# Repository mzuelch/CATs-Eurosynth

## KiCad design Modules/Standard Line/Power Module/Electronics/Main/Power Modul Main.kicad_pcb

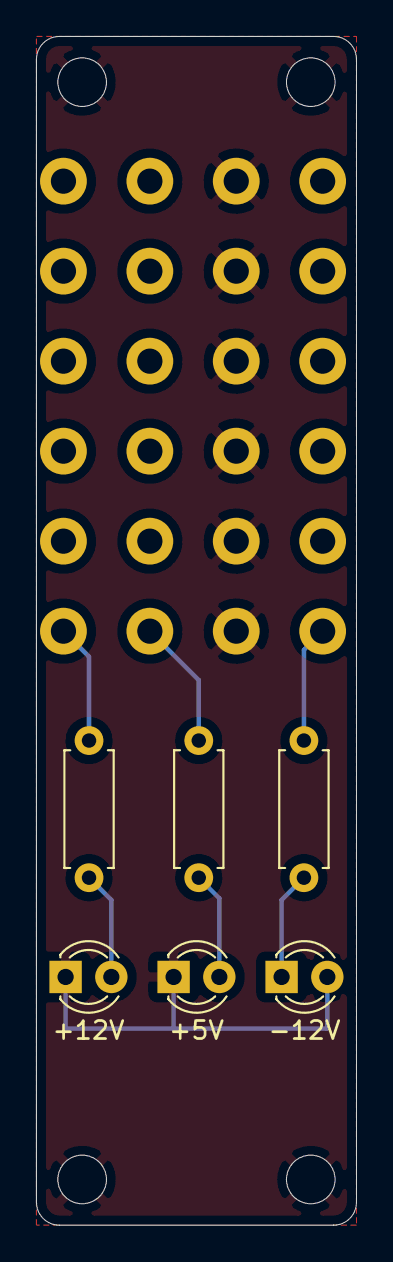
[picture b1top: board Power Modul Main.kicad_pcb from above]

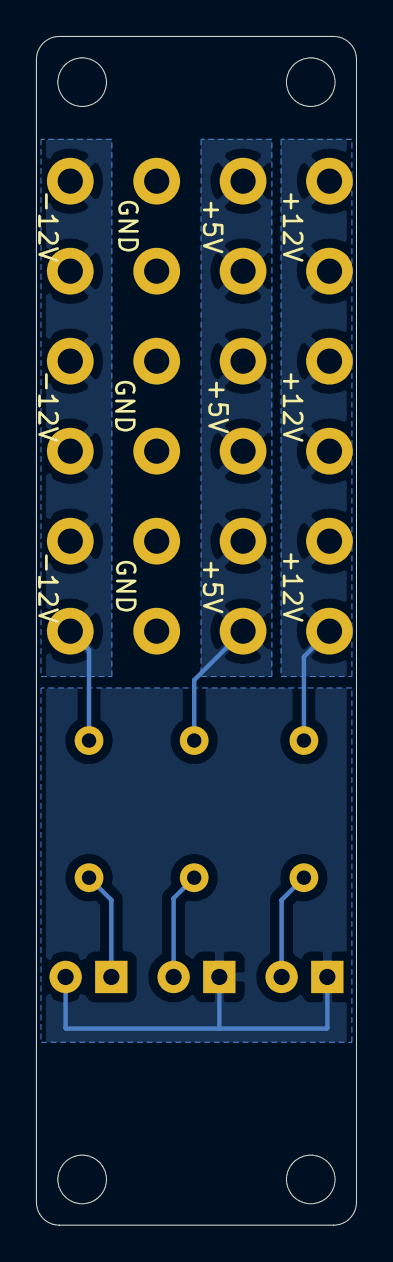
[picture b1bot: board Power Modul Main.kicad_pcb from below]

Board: 2 copper layers, 17.8 x 66.0 mm, 22 parts (4 on the bottom side), 7 nets.

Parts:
D1: +12V; LED_D3.0mm
D2: +5V; LED_D3.0mm
D3: -12V; LED_D3.0mm
H1, H2, H3, H4: MountingHole_Pad; MountingHole_2.7mm
J1, J5, J9: +12V; 03866b.68_6.3mm_FASTON
J2, J6, J10: +5V; 03866b.68_6.3mm_FASTON
J3, J7, J11: GND; 03866b.68_6.3mm_FASTON
J4, J8, J12: -12V; 03866b.68_6.3mm_FASTON
R1, R3: 1k; R_Axial_DIN0207_L6.3mm_D2.5mm_P7.62mm_Horizontal
R2: 200R; R_Axial_DIN0207_L6.3mm_D2.5mm_P7.62mm_Horizontal

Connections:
+5V: J2.1, J6.1, J10.1, R2.1
+12V: J1.1, J5.1, J9.1, R1.1
-12V: J4.1, J8.1, J12.1, R3.2
GND: D1.1, D2.1, D3.2, H1.1, H2.1, H3.1, H4.1, J3.1, J7.1, J11.1
unnamed: D1.2, R1.2
unnamed: D2.2, R2.2
unnamed: D3.1, R3.1

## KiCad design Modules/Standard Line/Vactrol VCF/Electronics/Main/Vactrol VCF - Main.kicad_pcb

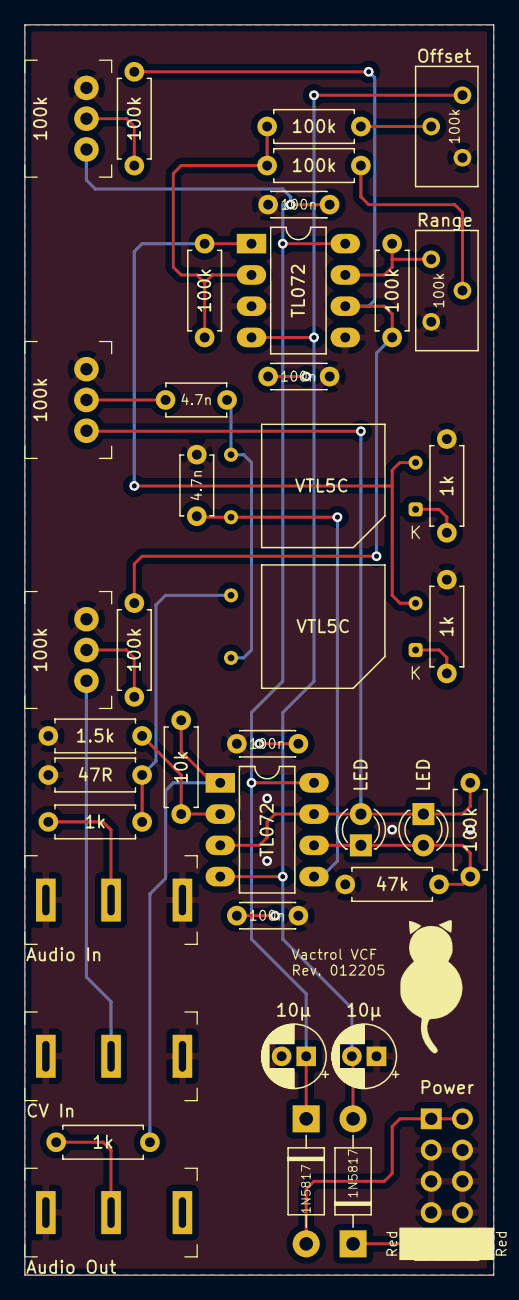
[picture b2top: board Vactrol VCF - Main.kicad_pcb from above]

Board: 2 copper layers, 38.1 x 101.6 mm, 40 parts (0 on the bottom side), 26 nets.

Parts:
C1, C2: 4.7n; C_Disc_D4.7mm_W2.5mm_P5.00mm
C3, C4: 10µ; CP_Radial_D5.0mm_P2.00mm
C5, C6, C7, C8: 100n; C_Disc_D4.3mm_W1.9mm_P5.00mm
D1, D2: LED; LED_D3.0mm
D3, D4: 1N5817; D_DO-41_SOD81_P10.16mm_Horizontal
J1: Audio In; Jack_3.5mm_QingPu_WQP-PJ323M
J2: Audio Out; Jack_3.5mm_QingPu_WQP-PJ323M
J3: Power; Power_2x5_Vertical
J4: CV In; Jack_3.5mm_QingPu_WQP-PJ323M
P1, P2, P3: 100k; Potentiometer_AlpsAlpine_RK0971110
R1, R3, R4, R12: 1k; R_Axial_DIN0207_L6.3mm_D2.5mm_P7.62mm_Horizontal
R2: 47R; R_Axial_DIN0207_L6.3mm_D2.5mm_P7.62mm_Horizontal
R5: 47k; R_Axial_DIN0207_L6.3mm_D2.5mm_P7.62mm_Horizontal
R6, R7, R8, R9, R13, R14, R15: 100k; R_Axial_DIN0207_L6.3mm_D2.5mm_P7.62mm_Horizontal
R10: 1.5k; R_Axial_DIN0207_L6.3mm_D2.5mm_P7.62mm_Horizontal
R11: 10k; R_Axial_DIN0207_L6.3mm_D2.5mm_P7.62mm_Horizontal
RV1, RV2: 100k; Potentiometer_Bourns_3296Y_Vertical
U1, U2: VTL5C; PerkinElmer_VTL5C
U3, U4: TL072; DIP-8_W7.62mm_LongPads

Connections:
+12V: C3.1, C5.1, C7.1, D3.1, P2.CW, U3.8, U4.8
-12V: C4.2, C6.2, C8.2, D4.2, RV1.3, U3.4, U4.4
GND: C2.1, C3.2, C4.1, C5.2, C6.1, C7.2, C8.1, J1.S, J1.TN, J2.S, J3.GND, J4.S, J4.TN, P1.CCW, P2.CCW, P3.CCW, R2.2, R3.1, R4.1, R5.1, R10.1, RV1.1, RV2.3, U3.3, U3.5
unnamed: C1.1, P1.W
unnamed: C1.2, U1.3, U2.4
unnamed: C2.2, U2.3, U4.5
unnamed: D1.1, D2.2, R5.2, R7.2, U4.6
unnamed: D1.2, D2.1, P1.CW, R7.1, U4.3, U4.7
unnamed: D3.2, J3.+12V
unnamed: D4.1, J3.-12V
unnamed: J1.T, R1.2
unnamed: J2.T, R12.1
unnamed: J4.T, P3.CW
unnamed: P2.W, R14.1
unnamed: P3.W, R15.1
unnamed: R1.1, R2.1, U1.4
unnamed: R3.2, U1.1
unnamed: R4.2, U2.1
unnamed: R6.1, R8.2, R9.2, U3.2
unnamed: R6.2, U1.2, U2.2, U3.1
unnamed: R8.1, RV1.2
unnamed: R9.1, RV2.2
unnamed: R10.2, R11.2, U4.2
unnamed: R11.1, R12.2, U4.1
unnamed: R13.1, R14.2, R15.2, U3.6
unnamed: R13.2, RV2.1, U3.7

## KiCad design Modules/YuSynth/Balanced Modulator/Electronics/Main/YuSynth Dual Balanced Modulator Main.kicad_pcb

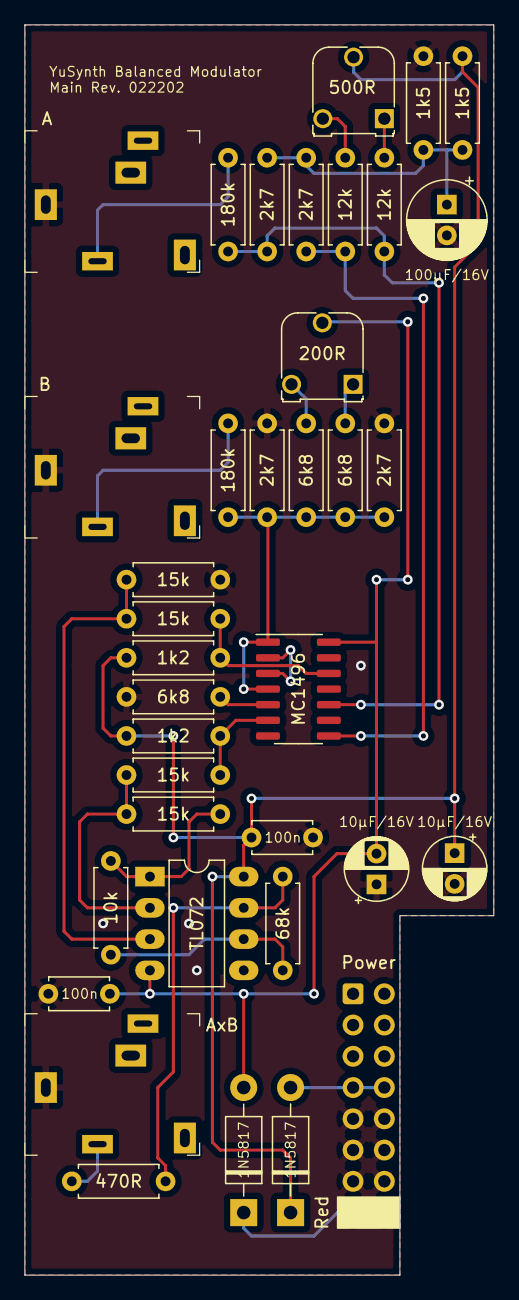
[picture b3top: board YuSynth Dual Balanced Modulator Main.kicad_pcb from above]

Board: 2 copper layers, 38.1 x 101.6 mm, 37 parts (0 on the bottom side), 25 nets.

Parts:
C1: 100µF/16V; CP_Radial_D6.3mm_P2.50mm
C2, C3: 10µF/16V; CP_Radial_D5.0mm_P2.50mm
C4, C5: 100n; C_Disc_D4.7mm_W2.5mm_P5.00mm
D1, D2: 1N5817; D_DO-41_SOD81_P10.16mm_Horizontal
J1: Power; Power_2x8_Horizontal
J2: A; Jack_3.5mm_QingPu_WQP-PJ324M
J3: B; Jack_3.5mm_QingPu_WQP-PJ324M
J4: AxB; Jack_3.5mm_QingPu_WQP-PJ324M
R1, R2: 1k5; R_Axial_DIN0207_L6.3mm_D2.5mm_P7.62mm_Horizontal
R3, R4: 180k; R_Axial_DIN0207_L6.3mm_D2.5mm_P7.62mm_Horizontal
R5, R7, R8, R12: 2k7; R_Axial_DIN0207_L6.3mm_D2.5mm_P7.62mm_Horizontal
R6, R10, R14: 6k8; R_Axial_DIN0207_L6.3mm_D2.5mm_P7.62mm_Horizontal
R9, R11: 12k; R_Axial_DIN0207_L6.3mm_D2.5mm_P7.62mm_Horizontal
R13, R15: 1k2; R_Axial_DIN0207_L6.3mm_D2.5mm_P7.62mm_Horizontal
R16, R17, R18, R19: 15k; R_Axial_DIN0207_L6.3mm_D2.5mm_P7.62mm_Horizontal
R20: 10k; R_Axial_DIN0207_L6.3mm_D2.5mm_P7.62mm_Horizontal
R21: 68k; R_Axial_DIN0207_L6.3mm_D2.5mm_P7.62mm_Horizontal
R22: 470R; R_Axial_DIN0207_L6.3mm_D2.5mm_P7.62mm_Horizontal
RV1: 200R; Potentiometer_Runtron_RM-065_Vertical
RV2: 500R; Potentiometer_Runtron_RM-065_Vertical
U1: MC1496; SOIC-14_3.9x8.7mm_P1.27mm
U2: TL072; DIP-8_W7.62mm_LongPads

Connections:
+6V: C1.1, R1.1, R2.2, R7.2, R8.2
+12V: C2.1, C4.1, D1.1, R1.2, R13.1, R15.1, RV2.2, U2.8
+12VA: D1.2, J1.+12V
-12V: C3.2, C5.2, D2.2, RV1.2, U1.14, U2.4
-12VA: D2.1, J1.-12V
GND: C1.2, C2.2, C3.1, C4.2, C5.1, J1.GND, J2.S, J3.S, J4.S, R2.1, R5.2, R12.1, R14.2, R18.1, U2.5
In_A: J2.T, R3.2
In_B: J3.T, R4.1
unnamed: R3.1, R8.1, R9.2, U1.10
unnamed: R6.2, RV1.3
unnamed: R9.1, RV2.1
unnamed: R4.2, R5.1, R6.1, R10.1, R12.2, U1.1, U1.4
unnamed: R10.2, RV1.1
unnamed: R11.1, RV2.3
unnamed: R7.1, R11.2, U1.8
unnamed: R13.2, R16.1, U1.6
unnamed: R14.1, U1.5
unnamed: R15.2, R17.2, U1.12
unnamed: R16.2, R19.2, U2.2
unnamed: R17.1, R18.2, U2.3
unnamed: R19.1, R20.2, U2.1
unnamed: R20.1, R21.2, U2.6
unnamed: R21.1, R22.2, U2.7
unnamed: U1.2, U1.3
Out: J4.T, R22.1

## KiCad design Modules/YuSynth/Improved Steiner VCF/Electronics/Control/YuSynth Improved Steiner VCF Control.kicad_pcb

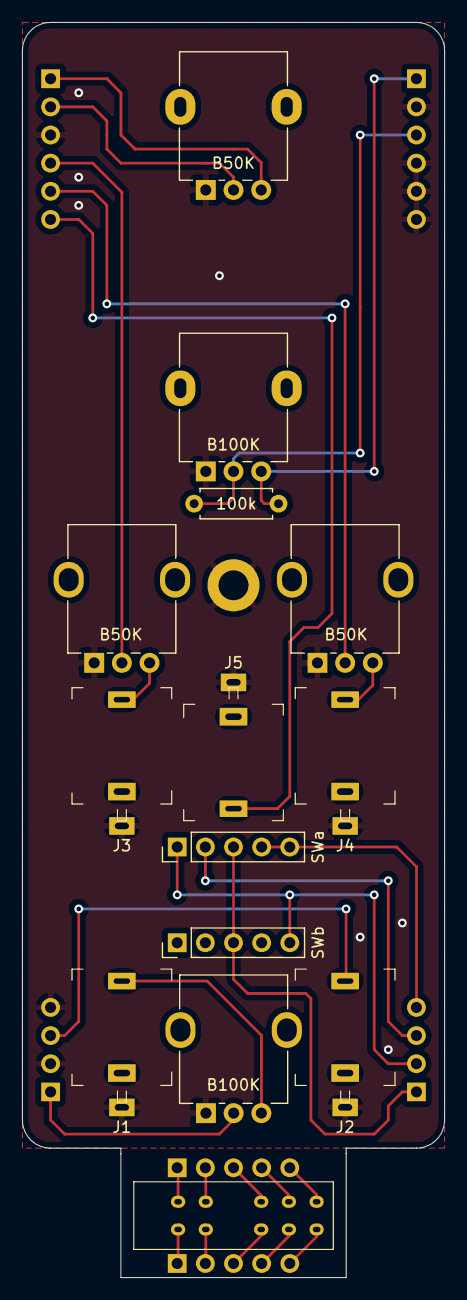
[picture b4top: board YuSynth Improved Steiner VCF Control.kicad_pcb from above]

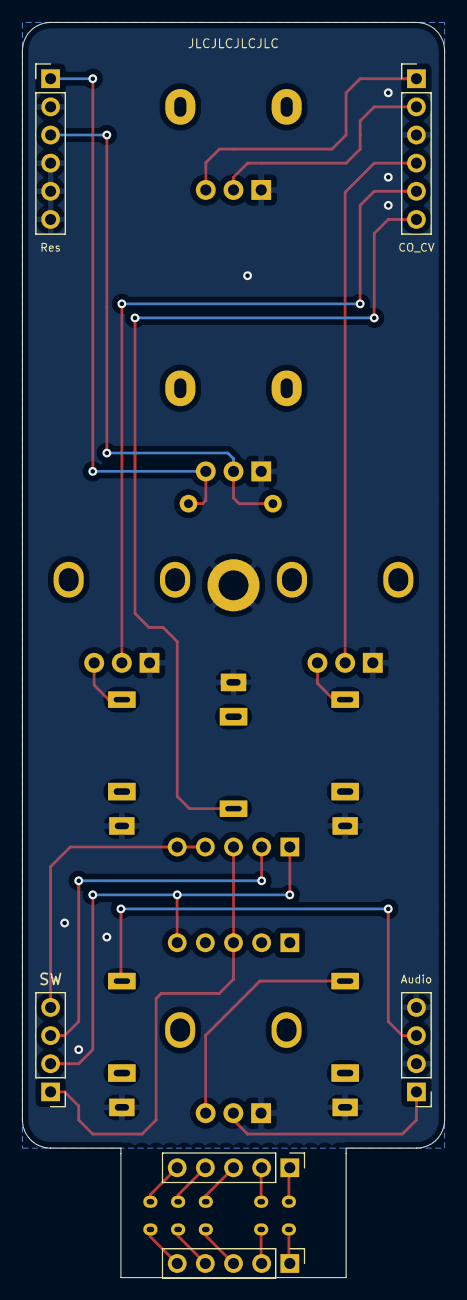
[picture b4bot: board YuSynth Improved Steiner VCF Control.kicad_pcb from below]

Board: 2 copper layers, 38.1 x 113.3 mm, 21 parts (6 on the bottom side), 22 nets.

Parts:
H1: MountingHole_Pad; MountingHole_2.7mm_M2.5_DIN965_Pad
J1: Audio In; Jack_3.5mm_QingPu_WQP-PJ301M-12
J2: Audio Out; Jack_3.5mm_QingPu_WQP-PJ301M-12
J3: CV#1; Jack_3.5mm_QingPu_WQP-PJ301M-12
J4: CV#2; Jack_3.5mm_QingPu_WQP-PJ301M-12
J5: V/Oct; Jack_3.5mm_QingPu_WQP-PJ301M-12
J6, J12: SWb; PinHeader_1x05_P2.54mm_Vertical
J7, J13: SWa; PinHeader_1x05_P2.54mm_Vertical
J8: Audio; PinHeader_1x04_P2.54mm_Vertical
J9: SW; PinHeader_1x04_P2.54mm_Vertical
J10: CO_CV; PinHeader_1x06_P2.54mm_Vertical
J11: Res; PinHeader_1x06_P2.54mm_Vertical
R1: 100k; R_Axial_DIN0207_L6.3mm_D2.5mm_P7.62mm_Horizontal
RV1, RV5: B100K; Potentiometer_Alpha_RD901F-40-00D_Single_Vertical
RV2, RV3, RV4: B50K; Potentiometer_Alpha_RD901F-40-00D_Single_Vertical
SW1: Mode; SS24E01-G5

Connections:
AudioOut: J2.T, J8.3
GND: H1.1, J1.S, J2.S, J3.S, J4.S, J5.S, J8.2, J8.4, J10.3, J11.2, J11.4, J11.5, J11.6, RV1.1, RV2.1, RV3.1, RV4.1, RV5.1
unnamed: J1.T, RV1.3
unnamed: J3.T, RV3.3
unnamed: J4.T, RV2.3
unnamed: J12.1, SW1.1
unnamed: J12.2, SW1.2
unnamed: J12.3, SW1.3
unnamed: J12.4, SW1.4
unnamed: J12.5, SW1.5
unnamed: J13.1, SW1.6
unnamed: J13.2, SW1.7
unnamed: J13.3, SW1.8
unnamed: J13.4, SW1.9
unnamed: J13.5, SW1.10
Res_In: J11.1, R1.1, RV5.3
Res_Out: J11.3, R1.2, RV5.2
SW_A: J6.5, J7.1, J9.2
SW_B: J7.2, J9.3
SW_C: J7.4, J7.5, J9.4
SW_In: J6.3, J7.3, J9.1
vOct: J5.T, J10.6
